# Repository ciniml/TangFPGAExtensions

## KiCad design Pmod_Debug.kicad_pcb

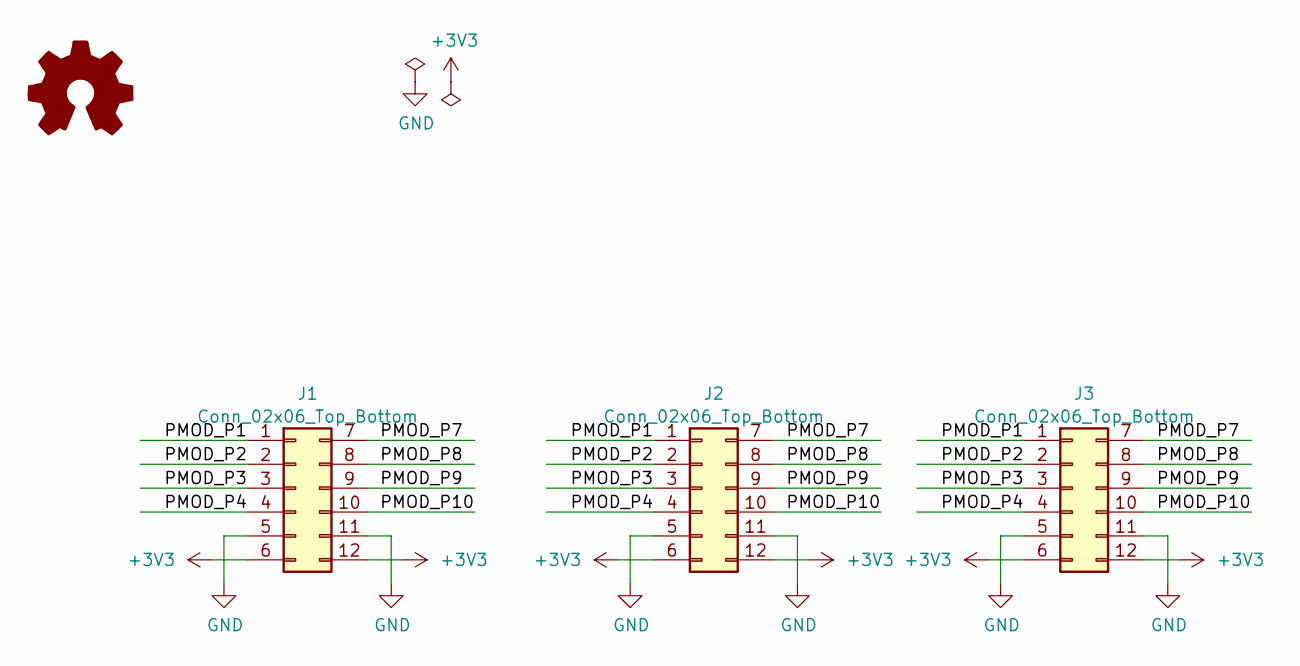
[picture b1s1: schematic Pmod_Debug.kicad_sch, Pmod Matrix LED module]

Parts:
J1: Conn_02x06_Top_Bottom; Conn_Pmod_Spec_B_Thin
J2: Conn_02x06_Top_Bottom; Conn_Pmod_Spec_D_Vertical_Thin
J3: Conn_02x06_Top_Bottom; Conn_Pmod_Spec_D_Thin
LOGO1: Logo_Open_Hardware_Small; logo

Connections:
+3V3: J1.6, J1.12, J2.6, J2.12, J3.6, J3.12
/PMOD_P1: J1.1, J2.1, J3.1
/PMOD_P2: J1.2, J2.2, J3.2
/PMOD_P3: J1.3, J2.3, J3.3
/PMOD_P4: J1.4, J2.4, J3.4
/PMOD_P7: J1.7, J2.7, J3.7
/PMOD_P8: J1.8, J2.8, J3.8
/PMOD_P9: J1.9, J2.9, J3.9
/PMOD_P10: J1.10, J2.10, J3.10
GND: J1.5, J1.11, J2.5, J2.11, J3.5, J3.11

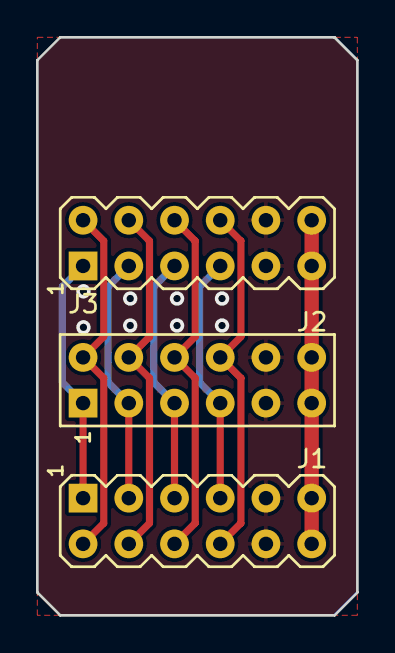
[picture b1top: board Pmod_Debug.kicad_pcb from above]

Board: 2 copper layers, 17.8 x 32.1 mm, 4 parts (1 on the bottom side), 10 nets.

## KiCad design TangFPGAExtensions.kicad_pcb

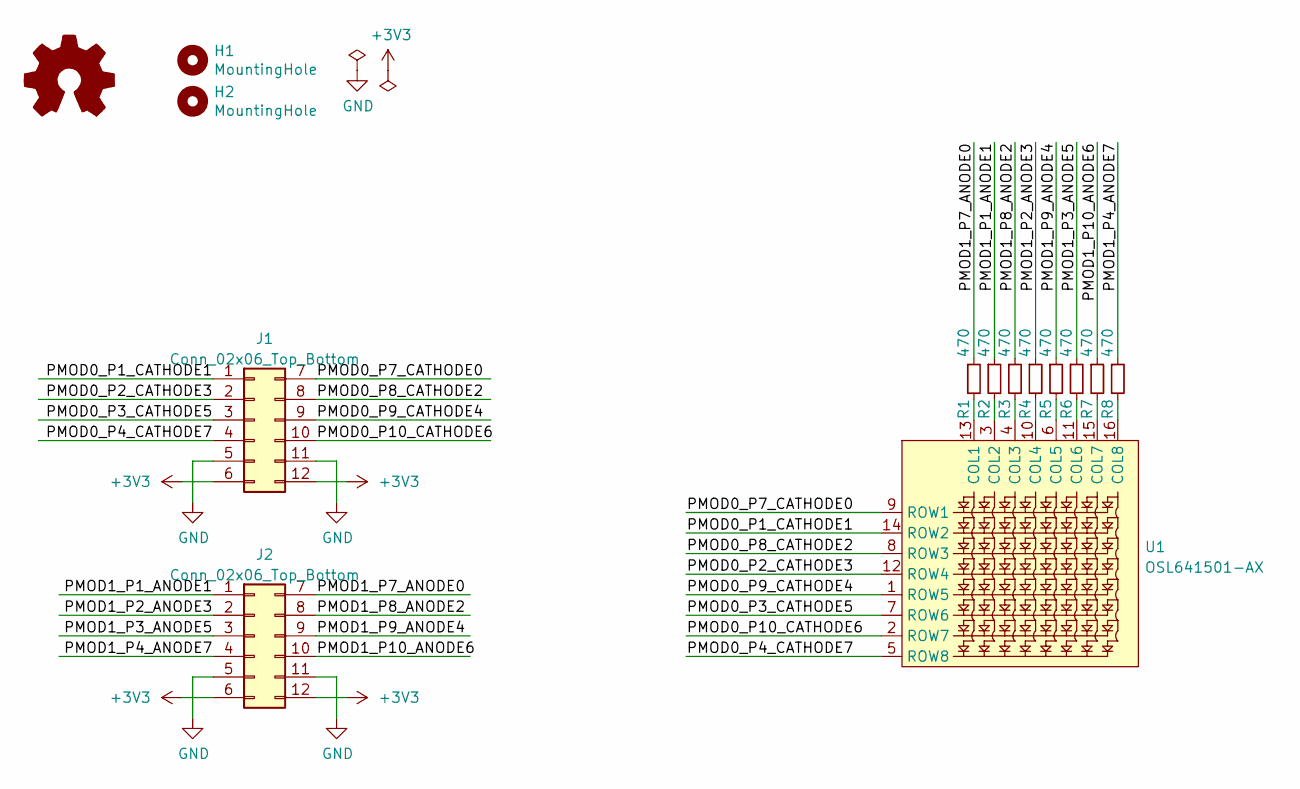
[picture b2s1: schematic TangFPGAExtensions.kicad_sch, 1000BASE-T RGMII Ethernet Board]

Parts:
H1, H2: MountingHole; MountingHole_3.2mm_M3_Mask
J1, J2: Conn_02x06_Top_Bottom; Conn_Pmod_Spec_B
LOGO1: Logo_Open_Hardware_Small; logo
R1, R2, R3, R4, R5, R6, R7, R8: 470; R_Axial_DIN0204_L3.6mm_D1.6mm_P5.08mm_Horizontal_with_1608m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
U1: OSL641501-AX

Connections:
+3V3: J1.6, J1.12, J2.6, J2.12
/PMOD0_P1_CATHODE1: J1.1, U1.14 (ROW2)
/PMOD0_P2_CATHODE3: J1.2, U1.12 (ROW4)
/PMOD0_P3_CATHODE5: J1.3, U1.7 (ROW6)
/PMOD0_P4_CATHODE7: J1.4, U1.5 (ROW8)
/PMOD0_P7_CATHODE0: J1.7, U1.9 (ROW1)
/PMOD0_P8_CATHODE2: J1.8, U1.8 (ROW3)
/PMOD0_P9_CATHODE4: J1.9, U1.1 (ROW5)
/PMOD0_P10_CATHODE6: J1.10, U1.2 (ROW7)
/PMOD1_P1_ANODE1: J2.1, R2.1
/PMOD1_P2_ANODE3: J2.2, R4.1
/PMOD1_P3_ANODE5: J2.3, R6.1
/PMOD1_P4_ANODE7: J2.4, R8.1
/PMOD1_P7_ANODE0: J2.7, R1.1
/PMOD1_P8_ANODE2: J2.8, R3.1
/PMOD1_P9_ANODE4: J2.9, R5.1
/PMOD1_P10_ANODE6: J2.10, R7.1
GND: J1.5, J1.11, J2.5, J2.11
unnamed: R1.2, U1.13 (COL1)
unnamed: R2.2, U1.3 (COL2)
unnamed: R3.2, U1.4 (COL3)
unnamed: R4.2, U1.10 (COL4)
unnamed: R5.2, U1.6 (COL5)
unnamed: R6.2, U1.11 (COL6)
unnamed: R7.2, U1.15 (COL7)
unnamed: R8.2, U1.16 (COL8)

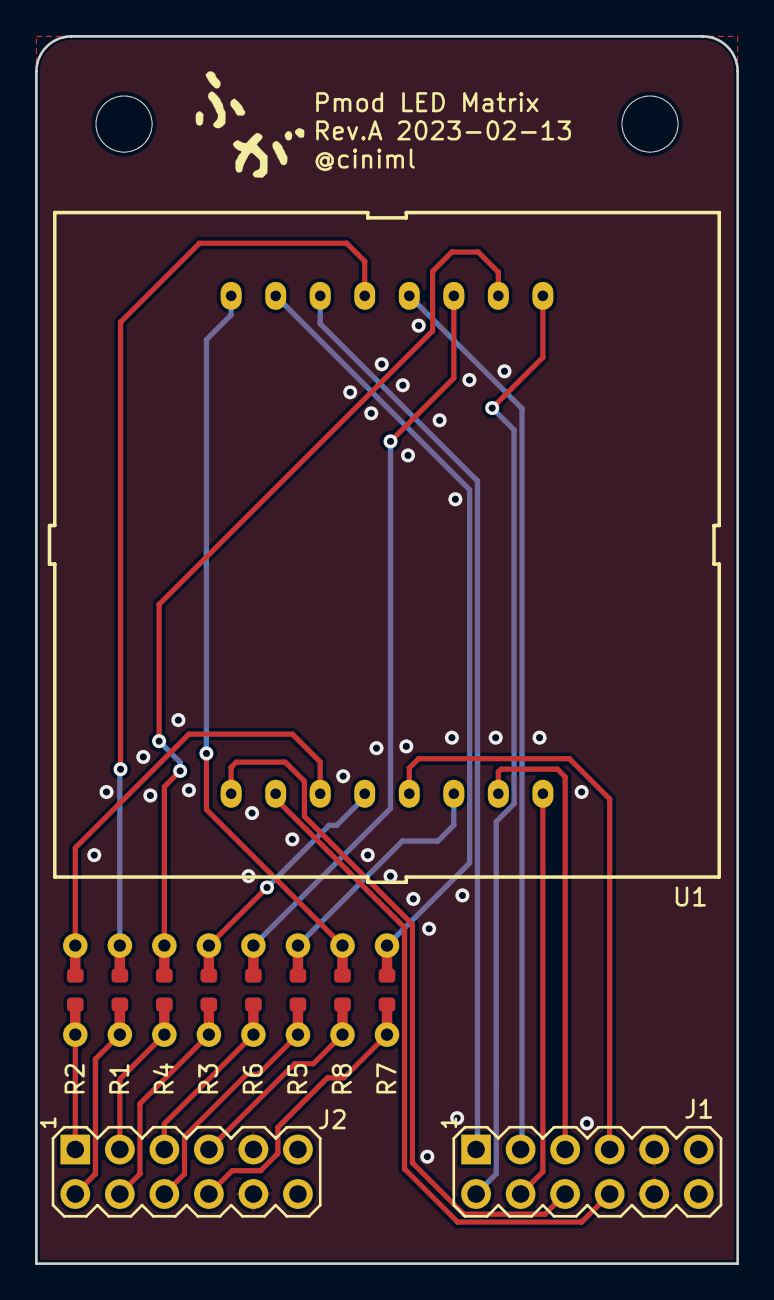
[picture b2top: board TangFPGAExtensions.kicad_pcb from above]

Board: 2 copper layers, 40.0 x 70.0 mm, 14 parts (0 on the bottom side), 26 nets.

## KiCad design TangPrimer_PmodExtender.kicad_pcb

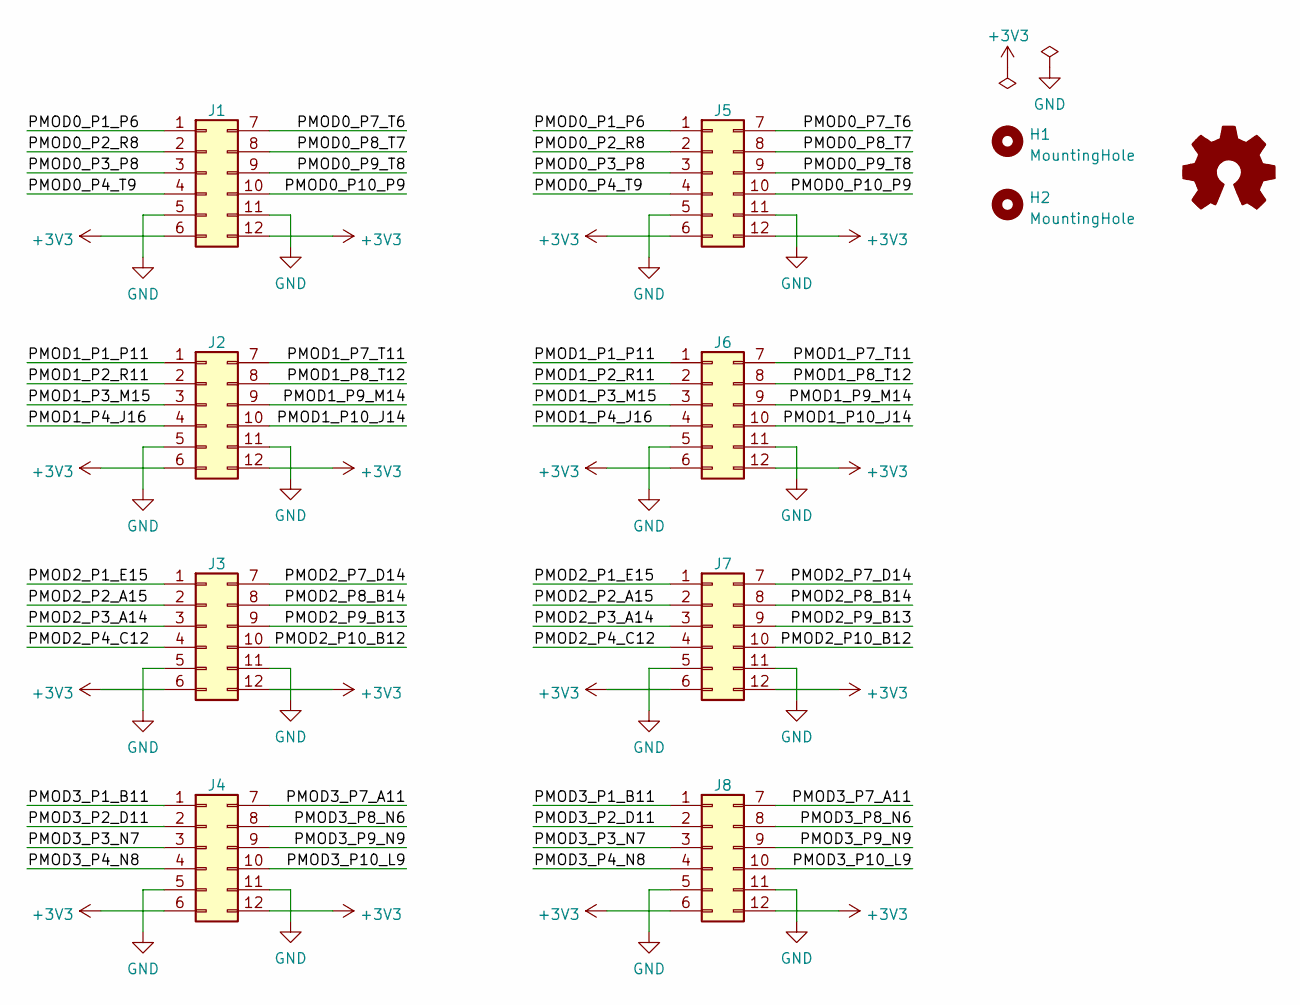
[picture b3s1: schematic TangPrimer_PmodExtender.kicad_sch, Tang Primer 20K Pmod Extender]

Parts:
H1, H2: MountingHole; MountingHole_3.2mm_M3_Mask
J1, J2, J3, J4: Conn_02x06_Top_Bottom; Conn_Pmod_Spec_B_Vertical_Thin
J5, J6, J7, J8: Conn_02x06_Top_Bottom; Conn_Pmod_Spec_D_Thin
LOGO1: Logo_Open_Hardware_Small; logo

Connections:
+3V3: J1.6, J1.12, J2.6, J2.12, J3.6, J3.12, J4.6, J4.12, J5.6, J5.12, J6.6, J6.12, J7.6, J7.12, J8.6, J8.12
/PMOD0_P1_P6: J1.1, J5.1
/PMOD0_P2_R8: J1.2, J5.2
/PMOD0_P3_P8: J1.3, J5.3
/PMOD0_P4_T9: J1.4, J5.4
/PMOD0_P7_T6: J1.7, J5.7
/PMOD0_P8_T7: J1.8, J5.8
/PMOD0_P9_T8: J1.9, J5.9
/PMOD0_P10_P9: J1.10, J5.10
/PMOD1_P1_P11: J2.1, J6.1
/PMOD1_P2_R11: J2.2, J6.2
/PMOD1_P3_M15: J2.3, J6.3
/PMOD1_P4_J16: J2.4, J6.4
/PMOD1_P7_T11: J2.7, J6.7
/PMOD1_P8_T12: J2.8, J6.8
/PMOD1_P9_M14: J2.9, J6.9
/PMOD1_P10_J14: J2.10, J6.10
/PMOD2_P1_E15: J3.1, J7.1
/PMOD2_P2_A15: J3.2, J7.2
/PMOD2_P3_A14: J3.3, J7.3
/PMOD2_P4_C12: J3.4, J7.4
/PMOD2_P7_D14: J3.7, J7.7
/PMOD2_P8_B14: J3.8, J7.8
/PMOD2_P9_B13: J3.9, J7.9
/PMOD2_P10_B12: J3.10, J7.10
/PMOD3_P1_B11: J4.1, J8.1
/PMOD3_P2_D11: J4.2, J8.2
/PMOD3_P3_N7: J4.3, J8.3
/PMOD3_P4_N8: J4.4, J8.4
/PMOD3_P7_A11: J4.7, J8.7
/PMOD3_P8_N6: J4.8, J8.8
/PMOD3_P9_N9: J4.9, J8.9
/PMOD3_P10_L9: J4.10, J8.10
GND: J1.5, J1.11, J2.5, J2.11, J3.5, J3.11, J4.5, J4.11, J5.5, J5.11, J6.5, J6.11, J7.5, J7.11, J8.5, J8.11

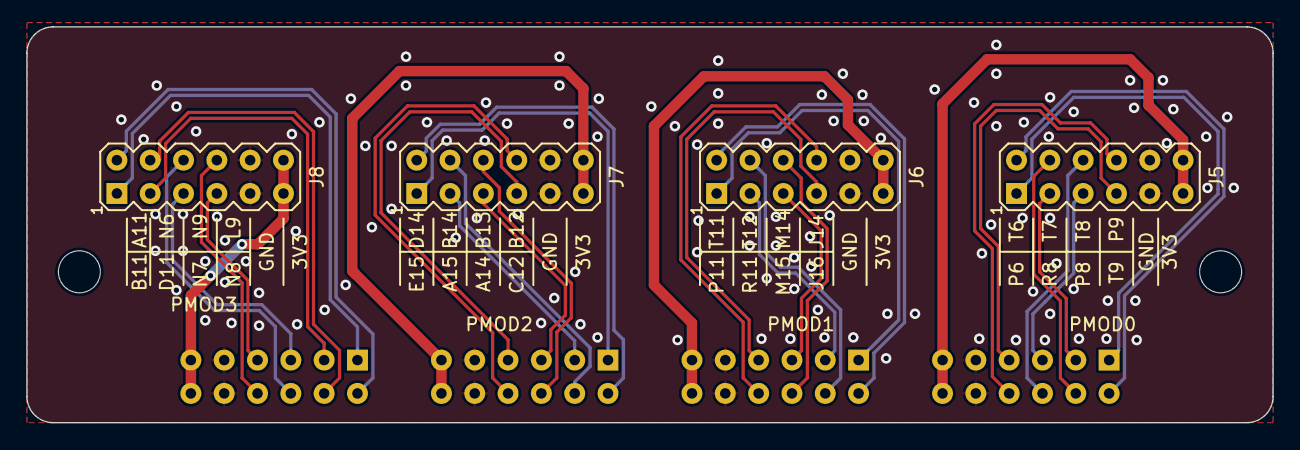
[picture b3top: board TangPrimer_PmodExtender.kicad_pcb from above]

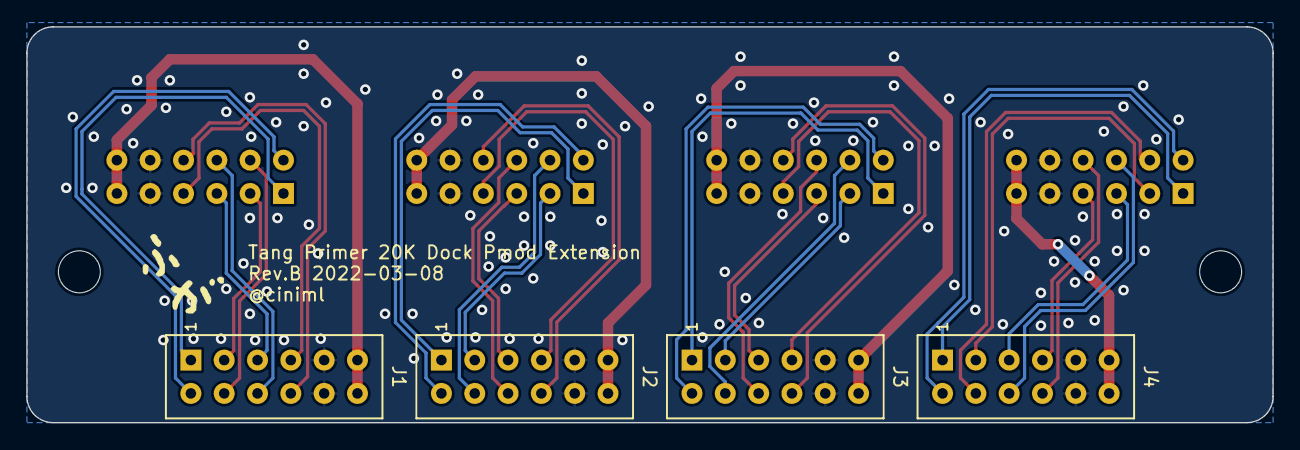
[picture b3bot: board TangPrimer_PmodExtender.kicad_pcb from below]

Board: 2 copper layers, 95.0 x 30.2 mm, 11 parts (5 on the bottom side), 34 nets.
